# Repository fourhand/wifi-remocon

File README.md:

# 에어컨 제어 시스템

## 설치 및 실행

### 1. Python 설치 (필수)

Python이 설치되어 있지 않은 경우:

1. [Python 공식 사이트](https://www.python.org/downloads/)에서 다운로드
2. 설치 시 **"Add Python to PATH"** 옵션을 **반드시 체크**하세요
3. 설치 완료 후 명령 프롬프트를 다시 시작하세요

### 2. 초기 설정 (권장)

가상환경을 생성하고 필요한 패키지를 설치합니다:

```bash
setup.bat
```

또는 단계별로:

```bash
# 가상환경 생성 및 패키지 설치
install-dependencies.bat
```

### 3. 서버 실행

```bash
start-server.bat
```

서버는 자동으로 가상환경을 활성화하고 실행됩니다.

### 가상환경 수동 사용

가상환경을 수동으로 활성화하려면:

```bash
venv\Scripts\activate.bat
```

비활성화하려면:

```bash
deactivate
```

### 4. 웹 브라우저에서 접속

- http://localhost:8000
- http://aircon-controller.local:8000 (mDNS 사용 시)

### 5. Windows 자동 시작 설정 (선택)

부팅할 때 자동으로 서버를 구동하려면 **관리자 권한** PowerShell(또는 명령 프롬프트)에서 아래 스크립트를 실행하세요.

```powershell
cd C:\Users\k\Documents\wifi-remocon
.\register-autostart.bat
```

- Windows 작업 스케줄러에 `WifiRemoconControlServer` 작업이 생성되며, 부팅 후 30초 뒤 `start-server.bat`을 SYSTEM 권한으로 실행합니다.
- 자동 시작을 해제하려면:

```powershell
cd C:\Users\k\Documents\wifi-remocon
.\unregister-autostart.bat
```

작업 상태 확인: `schtasks /Query /TN WifiRemoconControlServer`

## 문제 해결

### Python을 찾을 수 없는 경우

1. Python이 설치되어 있는지 확인: `python --version`
2. Python이 설치되어 있지만 PATH에 없는 경우:
   - `install-dependencies.bat` 또는 `start-server.bat` 실행 시
   - Python 실행 파일 경로를 직접 입력하라는 메시지가 나타납니다
   - 예: `C:\Python39\python.exe` 또는 `C:\Users\사용자명\AppData\Local\Programs\Python\Python39\python.exe`

### 서버가 실행되지 않는 경우

1. 필요한 패키지가 설치되어 있는지 확인: `pip list | findstr fastapi`
2. 포트 8000이 사용 중인지 확인: `netstat -ano | findstr :8000`
3. `start-server.bat`을 실행하여 오류 메시지 확인

### 브라우저에서 접근이 안되는 경우

1. 서버가 실행 중인지 확인
2. 방화벽 설정 확인
3. `http://127.0.0.1:8000`으로 접속 시도
4. 다른 브라우저로 시도

## API 엔드포인트

### 공통
- **Base URL**: `http://localhost:8000`
- **Content-Type**: `application/json`

### 요청 바디 스키마: AcCommand
- **power**: `"on"` | `"off"` (예: `"on"`)
- **mode**: 냉방/난방/제습/송풍/자동 등 장치가 이해하는 문자열 (예: `"cool"`)
- **temp**: 정수 온도 (예: `24`)
- **fan**: 풍량 (예: `"low"`, `"mid"`, `"high"`)
- **swing**: 풍향 (예: `"on"`, `"off"` 등)

필드는 모두 선택이며, 전달된 필드만 장치에 반영됩니다.

---

### GET /devices
- **설명**: 현재 발견된 장치 목록 조회
- **응답 예시**
```json
[
  {
    "id": "ac-01",
    "ip": "192.168.0.12",
    "port": 80,
    "last_seen": 1733980000.123
  }
]
```

### GET /devices/{device_id}/health
- **설명**: 특정 장치 Health 체크
- **응답 예시**
```json
{
  "device": "ac-01",
  "health": { "ok": true, "status_code": 200 }
}
```

### GET /devices/{device_id}/ac/state
- **설명**: 특정 장치의 현재 상태 조회
- **응답 예시**
```json
{
  "device": "ac-01",
  "ok": true,
  "state": {
    "power": "on",
    "mode": "cool",
    "temp": 24,
    "fan": "mid",
    "swing": "off"
  }
}
```

### GET /devices/status
- **설명**: 모든 장치의 상태를 한 번에 조회
- **응답 예시**
```json
[
  {
    "id": "ac-01",
    "ip": "192.168.0.12",
    "port": 80,
    "health": { "ok": true, "status_code": 200 },
    "state": {
      "power": "on",
      "mode": "cool",
      "temp": 24,
      "fan": "mid",
      "swing": "off"
    }
  }
]
```

### POST /devices/{device_id}/ac/set
- **설명**: 특정 장치 제어
- **바디**: `AcCommand`
- **응답 예시**
```json
{
  "device": "ac-01",
  "ip": "192.168.0.12",
  "params": { "power": "on", "mode": "cool", "temp": 24 },
  "result": {
    "ok": true,
    "status_code": 200,
    "attempts": 7,
    "all_results": [
      { "ok": true, "status_code": 200, "attempt": 1 }
      // ... 반복 전송 결과
    ]
  }
}
```

### POST /devices/control
- **설명**: 여러 장치를 한 번에 제어. 서버에서 병렬 처리 후 장치별 결과와 요약을 반환
- **바디**
```json
{
  "device_ids": ["ac-01", "ac-02"],
  "command": { "power": "on", "mode": "hot", "temp": 30 }
}
```
- **응답 예시**
```json
{
  "command": { "power": "on", "mode": "hot", "temp": 30 },
  "requested_ids": ["ac-01", "ac-02"],
  "target_ids": ["ac-01"],
  "missing": ["ac-02"],
  "summary": {
    "requested": 2,
    "attempted": 1,
    "succeeded": 1,
    "failed": 0,
    "missing": 1
  },
  "results": {
    "ac-01": { "ok": true, "status_code": 200, "attempts": 7, "all_results": [/* ... */] }
  }
}
```

### POST /all/on
- **설명**: 모든 장치를 켬. 기본값은 `{"power":"on","mode":"cool","temp":24}` 이며, 바디로 전달한 필드로 덮어쓸 수 있음
- **바디(선택)**: `AcCommand`
- **응답**: 각 장치별 결과 맵
```json
{
  "command": { "power": "on", "mode": "cool", "temp": 24 },
  "results": {
    "ac-01": { "ok": true, "status_code": 200, "attempts": 7, "all_results": [/*...*/] }
  }
}
```

### POST /all/off
- **설명**: 모든 장치를 끔
- **바디**: 없음
- **응답**: `/all/on`과 동일 형태로 각 장치별 결과 반환

### POST /webhook
- **설명**: 배포 스크립트(`deploy.sh`) 실행 트리거. 비동기로 실행되며, 서버는 즉시 응답.
- **응답 예시**
```json
{ "ok": true, "message": "Deployment started" }
```

---

### cURL 예시
```bash
# 장치 목록
curl -s http://localhost:8000/devices

# 특정 장치 상태
curl -s http://localhost:8000/devices/ac-01/ac/state

# 특정 장치 제어 (켜기)
curl -s -X POST http://localhost:8000/devices/ac-01/ac/set \
  -H "Content-Type: application/json" \
  -d '{"power":"on","mode":"cool","temp":24}'

# 모두 끄기
curl -s -X POST http://localhost:8000/all/off
```

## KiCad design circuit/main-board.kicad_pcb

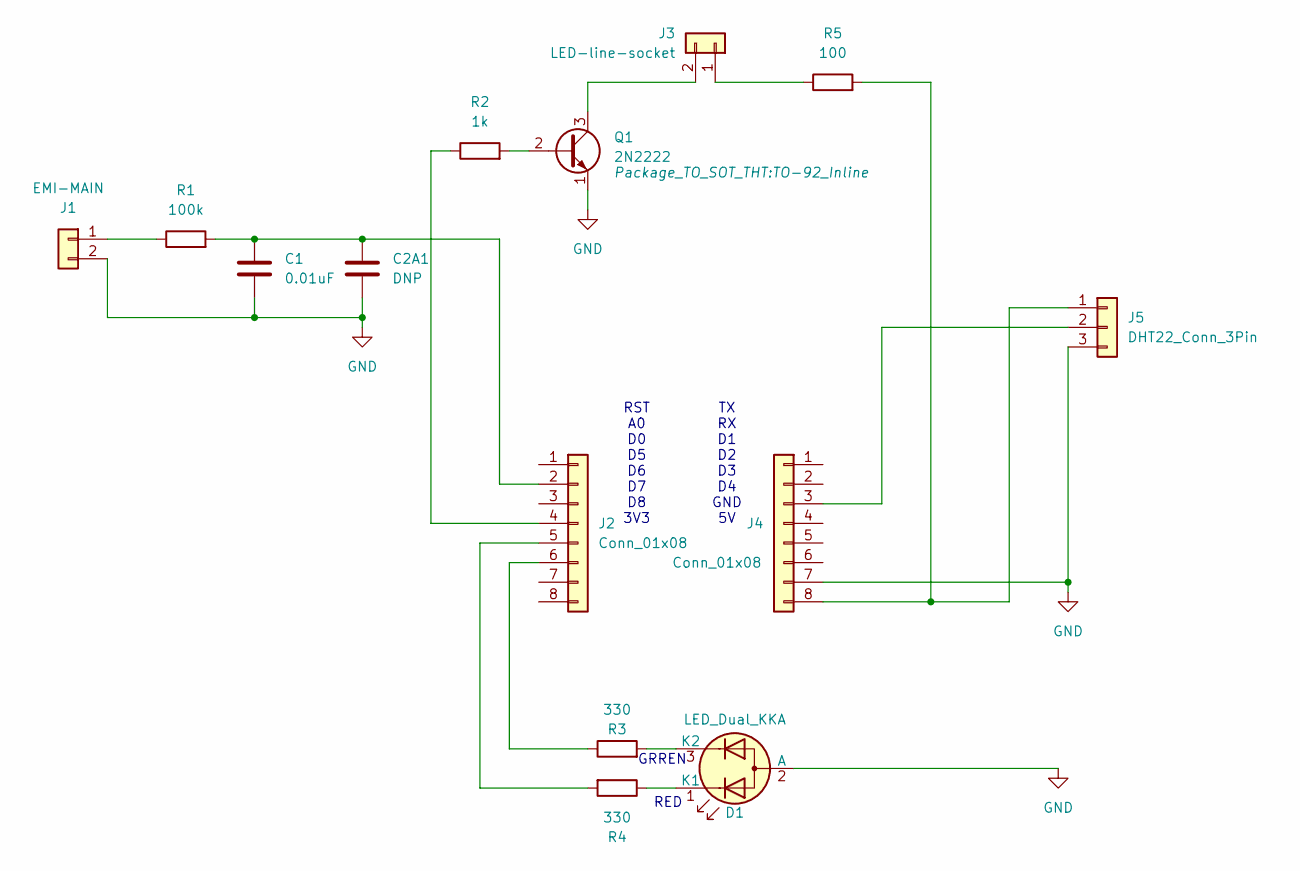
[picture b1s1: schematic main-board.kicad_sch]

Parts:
C1: 0.01uF; C_Disc_D5.0mm_W2.5mm_P2.50mm
C2A1: DNP; C_Disc_D5.0mm_W2.5mm_P2.50mm
D1: LED_Dual_KKA; LED_D5.0mm-3
J1: EMI-MAIN; U.FL_Hirose_U.FL-R-SMT-1_Vertical
J2, J4: Conn_01x08; PinHeader_1x08_P2.54mm_Vertical
J3: LED-line-socket; JST_PH_B2B-PH-K_1x02_P2.00mm_Vertical
J5: DHT22_Conn_3Pin; PinHeader_1x03_P2.54mm_Vertical
Q1: 2N2222; TO-92_Inline
R1: 100k; R_Axial_DIN0204_L3.6mm_D1.6mm_P5.08mm_Horizontal
R2: 1k; R_Axial_DIN0204_L3.6mm_D1.6mm_P5.08mm_Horizontal
R3, R4: 330; R_Axial_DIN0204_L3.6mm_D1.6mm_P5.08mm_Horizontal
R5: 100; R_Axial_DIN0204_L3.6mm_D1.6mm_P5.08mm_Horizontal

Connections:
GND: C1.2, C2A1.2, D1.2 (A), J1.2 (GND), J4.7, J5.3 (GND), Q1.1 (E)
unnamed: D1.1 (K1), R4.1
unnamed: D1.3 (K2), R3.2
unnamed: J1.1 (EMI_SIG), R1.1
unnamed: C1.1, C2A1.1, J2.2, R1.2
unnamed: J2.4, R2.1
unnamed: J2.5, R4.2
unnamed: J2.6, R3.1
unnamed: J3.1 (IR_LED+), R5.1
unnamed: J3.2 (IR_LED-), Q1.3 (C)
unnamed: J4.3, J5.2 (DATA)
unnamed: J4.8, J5.1 (VCC), R5.2
unnamed: Q1.2 (B), R2.2

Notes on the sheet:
TX RX D1 D2 D3 D4 GND 5V
RST A0 D0 D5 D6 D7 D8 3V3
GRREN
RED

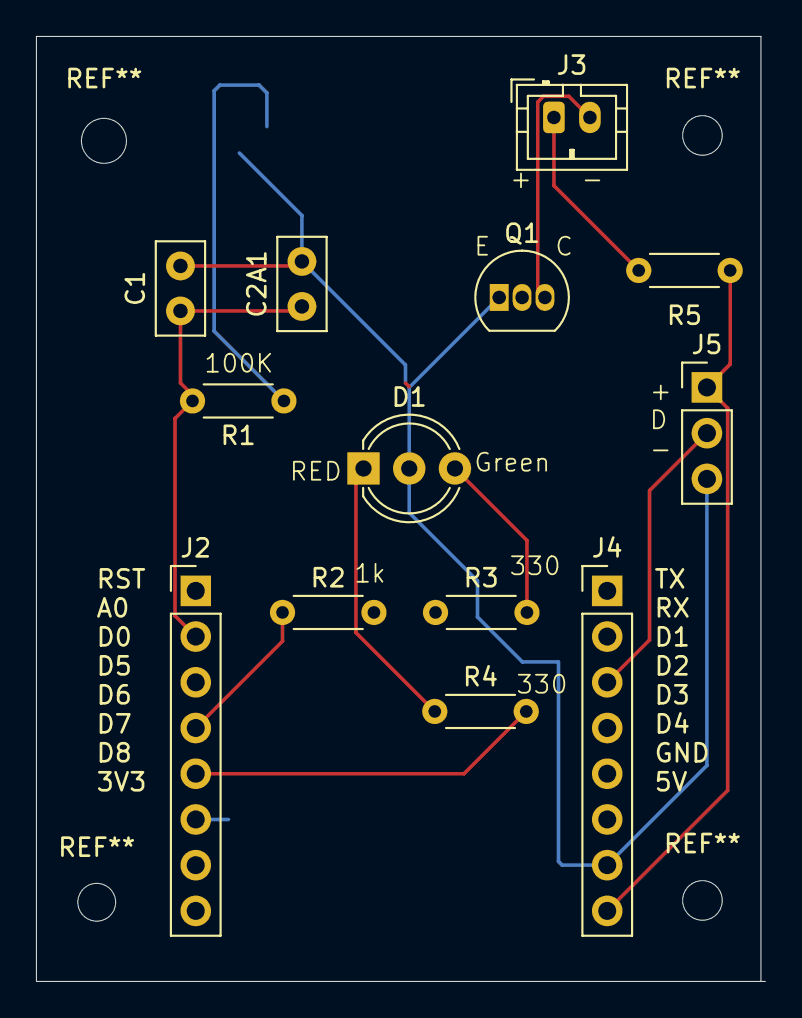
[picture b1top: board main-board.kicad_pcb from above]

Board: 4 copper layers, 40.5 x 52.5 mm, 14 parts (1 on the bottom side), 13 nets.

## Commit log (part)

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2025-11-21 Initial commit: WiFi remote control system
2025-12-12 에어콘 버튼위치 변경 배포기능 추가
2025-12-12 feat: 전체 제어 병렬화, UI 페이저/테마/가독성 개선 및 버튼 안전영역 처리 서버(control-server.py) 전체 제어 병렬 처리: /all/on, /all/off 내부 전송을 스레드 병렬화하고 per-device 타임아웃 추가 배치 제어 엔드포인트 추가: POST /devices/batch/ac/set (선택된 여러 장치 병렬 전송) 서버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
2025-12-12 예약기능 작업중
    백엔드
    SQLite 기반 예약 스케줄(1~7) 도입: 전원/모드/온도 + 1회/매일/매주 + 시작/종료 시각.
    API 추가: GET /schedules(목록), PUT /schedules/{sid}(업데이트).
    1분 주기 스케줄러: 시작/종료 시각에 맞춰 전체 제어, 5분간 매분 재전송으로 신뢰성 강화.
    1회 예약은 종료(OFF) 수행 후 자동 비활성화.
    DB 손상 대응: 무결성 검사 실패 시 자동 백업/재생성, 런타임 오류 시 복구 후 계속 동작.
2025-12-12 feat: 예약(7개) + SQLite/CRUD + 1분 스케줄러(5분 재전송) + 예약 UI/시간설정 + all-off 개선
2025-12-12 동작 로그
2025-12-13 update.sh에 git pull → 서비스 재시작 로직 일원화 서버의 배포 트리거도 update.sh 사용으로 전환
2025-12-13 schedule-list.sh 추가
2025-12-13 schedule-setting.sh status.sh
2025-12-13 스캐쥴에 Power 필드없에고 status.sh에 현재온도 값 추가
2025-12-13 요일명 수정
2025-12-13 all-on.sh all-off.sh 추가
2025-12-13 모듈별 정보 받은 시간 표시
2025-12-27 feat: add backend batch control api
2025-12-27 backend: add POST/PUT /devices/put_status ingest and GET /devices/get_status; switch discovery to 30s with http_port hint; cache-based health; client: reduce polling pending; firmware: unicast status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
2025-12-27 schedules: add start_date/end_date, migrate schema, accept in API, update scheduler and summary; GET /devices/get_status alias /devices/status
2025-12-27 web(schedule): colorize schedule cards by mode (hot/cool) and update dynamically on toggle
2025-12-27 backend: retry on failure for device commands (AC_SEND_ATTEMPTS, AC_SEND_INTERVAL_SEC with exponential backoff/jitter)
2025-12-27 web(schedule): support separate start_date/end_date (for once/daily/weekly), send via POST payload; populate modal from cache
2025-12-27 web(schedule): reorganize modal into two rows (시작일 시각 / 종요일 시각); dates always visible; weekly shows weekday row
2025-12-27 web(schedule): when schedule panel open, selecting device or 전체선택 switches back to control panel
2025-12-27 web: mark all devices with IP as pending on 전체 켜기/끄기 (was only those with room_temp), fixes UX where 특정 장치만 비활성화 보이던 문제
2026-01-04 feat: add wifi reconnect and autostart scripts
2026-01-09 esp8266: add cooperative serviceTick(); make WiFi connect non-blocking with timeout; improve reconnect flow (reconnect() first, then async begin) and call serviceTick during waits to prevent stalls
2026-01-09 esp8266: make WiFi fully non-blocking with simple state machine; enlarge UDP read buffer; use HTTPClient timeout for status push; start WiFi connect asynchronously in setup
2026-01-10 wdt: add SW watchdog (restart if no broadcast for 5m); feed HW WDT in loop; track last discover time
2026-01-13 PCB 작업
